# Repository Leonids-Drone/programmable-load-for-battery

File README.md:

## Specification
For prototype board

**Maximum input voltage (VBUS):** 30v

**Maximum continous current:** 50a

**Peak current:** 200a

## Control method
check programmable load - control board

## Cooling method
Water cooling or heat sink

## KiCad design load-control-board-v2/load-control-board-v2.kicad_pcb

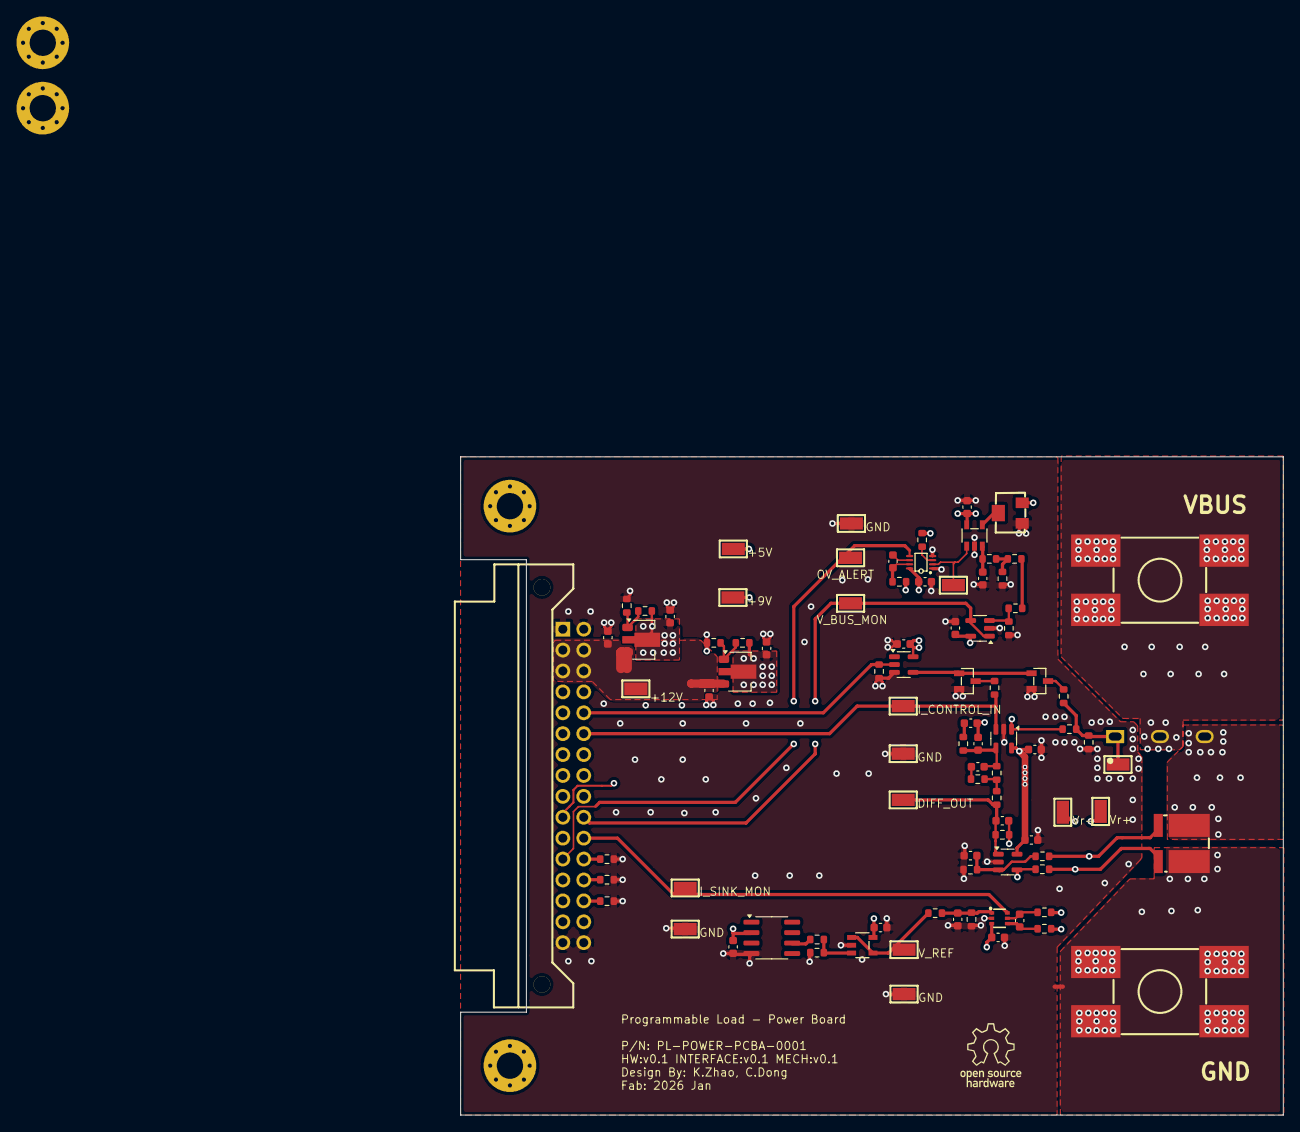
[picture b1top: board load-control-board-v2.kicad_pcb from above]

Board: 4 copper layers, 100.0 x 80.0 mm, 96 parts (0 on the bottom side), 45 nets.

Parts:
C1, C2, C4, C5, C7, C9, C10, C11, C12, C14, C17, C21: 100n; C_0603_1608Metric
C3, C6, C8, C49: 1u; C_0603_1608Metric
C13, C15: 100p; C_0603_1608Metric
C16: 47n; C_0603_1608Metric
C18: 1n; C_0603_1608Metric
C19, C20: 10n; C_0603_1608Metric
C53: 1u; R_0603_1608Metric
CN1: 3511232BMRS0BNA2; CONN-TH_3511232BMRS0BNA2
CN2, CN3: BTC22M4NBB4SCM; CONN-SMD_L10.8-W10.0-LS17.4
H1, H5, H9, H13: MountingHole_Pad; MountingHole_3.2mm_M3_Pad_Via
NT1: NetTie_2; NetTie-2_SMD_Pad0.5mm
Q1, Q2: AO3400A; SOT-23-3_L2.9-W1.3-P1.90-LS2.4-BR
Q3: IRFP7530PBF; PG-TO247-3_L15.9-W5.2-P5.44-L_1_Horizontal
R1: R; R_0603_1608Metric
R2, R6: 240; R_0603_1608Metric
R3: 720; R_0603_1608Metric
R4: 11k; R_0603_1608Metric
R5, R12, R15, R17, R18, R22, R25: 1k; R_0603_1608Metric
R7: 1488; R_0603_1608Metric
R8, R19, R24, R27, R28: 0; R_0603_1608Metric
R9: 3224W-1-103E; RES-ADJ-SMD_3224W
R10, R13, R29, R76, R77, R78: 10k; R_0603_1608Metric
R11: 24k; R_0603_1608Metric
R14: 11.5k; R_0603_1608Metric
R16, R20: 40k; R_0603_1608Metric
R21: 47; R_0603_1608Metric
R23: 500; R_0603_1608Metric
R26, R72: 100; R_0603_1608Metric
R_SHUNT1: BVB-M-R001-1.0; RES-SMD_4P-L6.9-W6.6_SBB-K-2F-N-T5
TP0a1: I_SINK_MON; SMD_RH-5015
TP0c1: I_CONTROL_IN; SMD_RH-5015
TP1: +12v; SMD_RH-5015
TP2: DIFF_OUT; SMD_RH-5015
TP3: MOS_G; SMD_RH-5015
TP10: +5v; SMD_RH-5015
TP11: +9v; SMD_RH-5015
TP12: V_SHUNT_P; SMD_RH-5015
TP16: V_SHUNT_N; SMD_RH-5015
TP20, TP21, TP22, TP26: GND; SMD_RH-5015
TP30: REF; SMD_RH-5015
TP31: V_BUS_MON; SMD_RH-5015
TP32: VBUS_COMP_OUT; SMD_RH-5015
TP33: OV_ALERT; SMD_RH-5015
U1, U3: LM317_SOT-223; SOT-89-3
U2: 74AHC1G04; SOT-23-5
U5: REF5025AD; SOIC-8_3.9x4.9mm_P1.27mm
U6: SN74LVC1G123DCUR_C352969; VSSOP-8_L2.3-W2.0-P0.50-LS3.1-BL
U7: ALERT_COMP_OUT; SOT-23-5_L2.9-W1.6-P0.95-LS2.8-TL
U8, U10, U11: OPA188xxDBV; TSOT-23-5
U12: INA186A1IDCKR; SC-70-6_L2.2-W1.3-P0.65-LS2.1-BR
U22: TL081HIDBVR; SOT-23-5_L2.9-W1.6-P0.95-LS2.8-TL

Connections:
+5V: C2.2, C3.1, C7.2, C8.1, C10.2, C12.2, C21.2, C49.1, CN1.10 (A10), R2.1, R9.3, R10.1, R13.2, TP10.1, U1.2 (VO), U2.5 (VCC), U5.2 (Vin), U6.8 (VCC), U7.5 (V+), U8.5 (V+), U12.3 (VS), U22.5 (V+)
+9V: C6.1, C14.2, C17.2, R6.1, TP11.1, U3.2 (VO), U10.5 (V+), U11.5 (V+)
+12V: C1.1, C4.1, CN1.2 (A2), CN1.3 (A3), CN1.18 (B2), CN1.19 (B3), TP1.1, U1.3 (VI), U3.3 (VI)
/I_SINK_MON_CH0: CN1.27 (B11), TP0a1.1, U12.6 (OUT)
/I_SINK_MON_CH1: CN1.28 (B12), R76.1
/I_SINK_MON_CH2: CN1.29 (B13), R77.1
/I_SINK_MON_CH3: CN1.30 (B14), R78.1
/ch0/MOS_G: Q3.1 (G), R24.2, R26.2, R29.2, TP3.1
/ch0/V_REF_FIL: C11.1, C53.1, R72.2, U12.1 (REF)
/ch0/V_Rs0n: R18.2, R28.2, R_SHUNT1.3, TP16.1
/ch0/V_Rs0p: R17.2, R27.2, R_SHUNT1.4, TP12.1
ENABLE: CN1.21 (B5), R1.1, U2.2
GND: C1.2, C2.1, C3.2, C4.2, C5.1, C6.2, C7.1, C8.2, C10.1, C11.2, C12.1, C13.2, C14.1, C17.1, C21.1, C49.2, C53.2, CN1.1 (A1), CN1.16 (A16), CN1.17 (B1), CN1.32 (B16), NT1.2, Q1.2 (S), Q2.2 (S), R1.2, R3.2, R5.1, R7.2, R9.1, R12.2, R15.1, R16.2, R29.1, R76.2, R77.2, R78.2, TP20.1, TP21.1, TP22.1, TP26.1, U2.3 (GND), U5.4 (GND), U6.1 (~A), U6.4 (GND), U7.2 (V-), U8.2 (V-), U10.2 (V-), U11.2 (V-), U12.2 (GND), U22.2 (V-)
GNDPWR: CN3.1, CN3.2, CN3.3, CN3.4, NT1.1, R_SHUNT1.2
I_CONTROL: CN1.22 (B6), R19.2, TP0c1.1, U11.3 (+)
unnamed: C15.1, R20.1, R21.2, TP2.1, U10.1
unnamed: C16.2, R22.1
unnamed: C18.1, C19.1, R26.1, U11.1
unnamed: C19.2, R25.2
unnamed: Q1.3 (D), R19.1
unnamed: Q2.3 (D), R24.1
unnamed: Q3.3 (S), R_SHUNT1.1
unnamed: R4.2, R5.2, R8.1
unnamed: R21.1, R22.2, R23.2
unnamed: R2.2, R3.1, U1.1 (ADJ)
unnamed: R6.2, R7.1, U3.1 (ADJ)
unnamed: R11.1, U5.6 (Vout)
unnamed: TP32.1, U6.2 (B), U7.1 (OUT)
unnamed: C9.2, U6.6 (Cext)
unnamed: C9.1, R13.1, U6.7 (Rext/Cext)
unnamed: R10.2, U6.3 (~CLR)
unnamed: C5.2, R8.2, U7.3 (IN+)
unnamed: R9.2, U7.4 (IN-)
unnamed: R14.2, R15.2, U8.3 (+)
unnamed: C13.1, R16.1, R17.1, U10.3 (+)
unnamed: C15.2, R18.1, R20.2, U10.4 (-)
unnamed: C16.1, C18.2, R23.1, R25.1, U11.4 (-)
unnamed: C20.1, R27.1, U12.4 (IN+)
unnamed: C20.2, R28.1, U12.5 (IN-)
unnamed: R11.2, R12.1, U22.3 (IN+)
OV_ALERT: CN1.12 (A12), TP33.1, U6.5 (Q)
VBUS: CN2.1, CN2.2, CN2.3, CN2.4, Q3.2 (D), R4.1, R14.1
V_BUS_MON: CN1.26 (B10), TP31.1, U8.1, U8.4 (-)
V_REF: R72.1, TP30.1, U22.1 (OUT), U22.4 (IN-)
~ENABLE: Q1.1 (G), Q2.1 (G), U2.4

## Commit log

2025-11-27 Init
2025-11-27 Simple voltage source
2025-11-27 Update gitignore
2025-11-27 add ignore
2025-11-30 First L-C simulation try
2025-12-01 Tuning the LC value
2025-12-02 test
2025-12-08 create load board v1
2025-12-08 opamp part
2025-12-08 Update ignore
2025-12-09 Add digital-control-board
2025-12-09 delet digital control board
2025-12-09 recreate
2025-12-09 Get some design from rp minimal board
2025-12-09 Update sch
2025-12-09 communicate 1
2025-12-12 Update digital-control-board
2025-12-12 Create simulation and move relative files
2025-12-12 simulation double opamp
2025-12-13 update common lib
2025-12-13 sch half complete
2025-12-13 First try of two stage opa
2025-12-14 ac analysis
2025-12-14 Add simulate parameters
2025-12-14 Add ADC input filter
2025-12-14 upload C513170 to lib
2025-12-15 Remove auto save
2025-12-16 pre-final sch
    add channel 0-4
2025-12-16 push channel.kiacd_sch
2025-12-16 lc2kicad
2025-12-16 temp push
2025-12-17 Edit multi opamp
2025-12-17 Rearrange design in load control board, need further check
2025-12-19 Sch pre-finish, without connector label
2025-12-19 Move to layout stage
2025-12-24 initial layout
2025-12-25 final layout and initial connecting
2025-12-25 Import from Dong's windows computer lib
2026-01-02 Add connector
2026-01-02 edit esc-lib
2026-01-06 Reset lib to useable state, add C963694 and C963693 to lib
    git restore --source 2908f185c442d5d7c429a6014c4036d19cda51b5 -- /Users/kelvin-zhao/Development/git/_Leonids/programmable-load-for-battery/programmable-load-library.kicad_sym
2026-01-07 Define the connector pinout to control board, import current connector
2026-01-07 layout before check
2026-01-07 layout adjust
2026-01-07 Section upload
    Monostable Multivibrator for OV, VBUS scale resistor network and buffer Opa
2026-01-08 Change layout of LDO and VBUS monitor
2026-01-08 Add filled zone for mosfet, change terminal to from THO to SMT
2026-01-09 Complete second times layout (no copper filled)
2026-01-10 connection and drc check
    connection of power layer is done
    drc checked
2026-01-11 First complete PCB, DRC check complete
2026-01-11 Add design info and logo
2026-01-11 Correct the 3D model of components
2026-01-11 Correcr INA186A1IDCKR to A2
    50V/V is the correct gain
2026-01-11 Change INA back to 25V/V, change diff gain to 1:40
2026-03-16 Add 4channel
2026-03-24 Move from load-control-board-v1 to v2
2026-03-24 Add 2011 heat sink
